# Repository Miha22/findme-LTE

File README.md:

# Low power LTE & GNSS anti-theft tracker

This project contains hardware design files, including schematics and PCB layouts created by Deniel.  
It is shared for educational and personal use purposes only. Commercial use is not permitted without written permission.

## Preview

The previews of the PCB design and schematic:

>  Note: The project is ongoing
> 1. Current schematic revision v0.3
> 2. Current PCB revision v0.1

## Description
Very compact __(20mm x 90mm)__ LTE modem designed to be used as anti-theft geolocation tracker to be mounted inside bicycles, moto, scooters etc. The UDP server and client to be setup and installed.

## Main Hardware
- MCU: STM32L433CCT6
- LTE: SIM7020**E**
- GNSS: ATGM336H-6N-74

## Notes for You
1. The design is still in Alpha state. New updates and revisions coming.
2. Firmware to be developed and tested as well as remote UDP server.
3. Real life Antenna test and adjustments needed, impedance matching has to be tuned (footprints are present).
4. Includes Design Rules errors due to **extreme size constraints**, take that in mind evaluating/redesigning the PCB. Keep width <25mm. 
5. All parts' datasheets have been analyzed. 
6. All parts are in stock on jlcpcb.com (except SIM7020E, but available on aliexpress for 9$+shipping).
7. Many drafts schematics are included in backups for you to see. Many failed because of incompatibility.

## License
This project is provided under a custom license based on the MIT License.  
Commercial use is prohibited. See the [LICENSE](./LICENSE) file for full details.

---

**Copyright © 2025 Deniel A.**

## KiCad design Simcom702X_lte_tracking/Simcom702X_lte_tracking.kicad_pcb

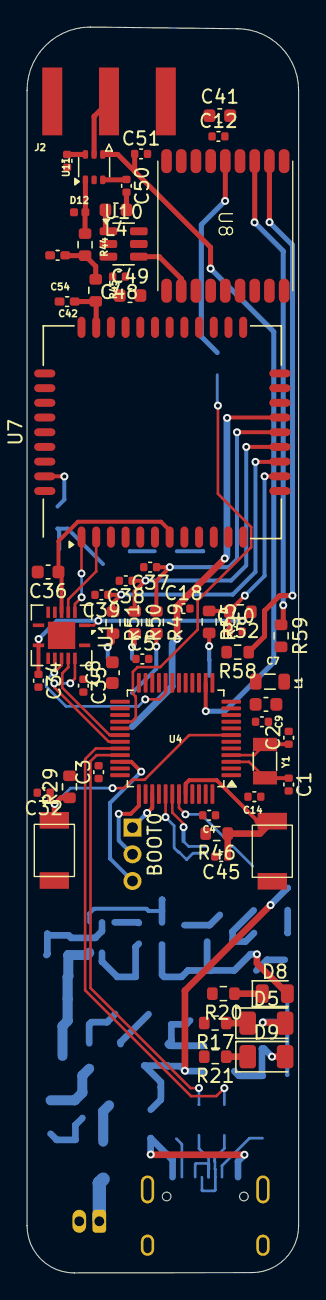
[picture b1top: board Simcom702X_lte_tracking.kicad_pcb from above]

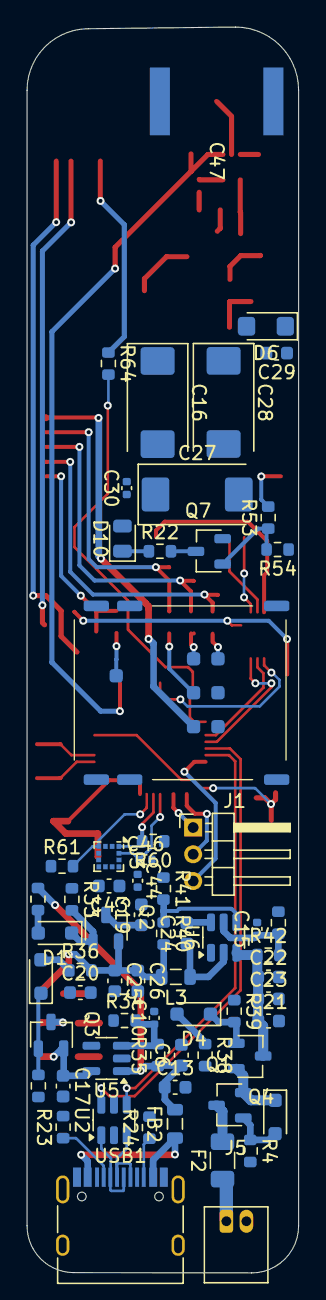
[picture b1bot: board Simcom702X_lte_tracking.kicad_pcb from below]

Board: 4 copper layers, 20.3 x 93.2 mm, 122 parts (64 on the bottom side), 78 nets.

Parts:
BOOT0: TS-1088-AR02016; SPST_39x30mm
C1, C2: 15p; C_0402_1005Metric
C3, C4, C5, C12, C14, C18, C30, C32, C34, C35, C40, C44, C45, C46, C47, C48: 0.1u; C_0402_1005Metric
C6, C7, C17, C29, C49: 1u; C_0603_1608Metric
C8: 4.7u; C_0603_1608Metric
C9: 0.01u; C_0402_1005Metric
C10, C15: 1n; C_0402_1005Metric
C13, C19, C20, C21, C24, C36: 0.1u; C_0603_1608Metric
C16, C27, C28: 100u; CP_EIA-7343-31_Kemet-D
C22, C23, C41, C43: 10u; C_0603_1608Metric
C25, C26: 22u; C_0603_1608Metric
C37, C38, C39: 22p; C_0402_1005Metric
C42, C54: 0u; C_0402_1005Metric_Pad0.74x0.62mm_HandSolder
C50: 470p; C_0402_1005Metric
C51: 100p; C_0402_1005Metric
D1: 1N5819WS; D_SOD-323_HandSoldering
D2: MM3Z10; D_SOD-323_HandSoldering
D3, D4: 1N5817WS; D_SOD-323_HandSoldering
D5: XL-3216SURC; LED_1206_3216Metric
D6: SMF6.0A; D_SMF
D8: XL-2012UYC; LED_0805_2012Metric
D9: XL-3216UOC; LED_1206_3216Metric
D10: XL-2012UBC-A; LED_0805_2012Metric
D12: LXES15AAA1-153; DFN1006-2L-BI
F2: JFC1206-1500FS; Fuse_1206_3216Metric
FB2: CBW201209U152T; L_0805_2012Metric
J1: SWD; PinHeader_1x03_P2.00mm_Horizontal
J2: SMA; SMA_Amphenol_132289_EdgeMount
J4: SNO-1470; nanoSIM_SNO-1470
J5: S2B-ZR-3.4(LF)(SN); JST_ZH_S2B-ZR_1x02_P1.50mm_Horizontal
L1: 39n; L_0805_2012Metric
L3: 4.7u; L_0805_2012Metric
L4: 7.5n; L_0603_1608Metric
NRST1: TS-1088-AR02016; SPST_39x30mm
Q1, Q2, Q3, Q4: AO3401A; SOT-23
Q7: AO3400A; SOT-23
R4, R33, R34, R37, R39, R43: 100k; R_0603_1608Metric
R17, R20, R21: 220; R_0603_1608Metric
R22, R58, R59: 100; R_0603_1608Metric
R23, R24: 5.1k; R_0603_1608Metric
R29, R32, R35, R36, R38, R41, R42, R46, R52, R60, R61: 10k; R_0603_1608Metric
R40: 33.2k; R_0603_1608Metric
R44, R45: 0; R_0603_1608Metric
R49, R50, R51: 22; R_0603_1608Metric
R53: 4.7k; R_0603_1608Metric
R54: 47k; R_0603_1608Metric
R55, R64: 1k; R_0603_1608Metric
U1: TXB0104RGYR; Texas_S-PVQFN-N14
U2: USBLC6-2SC6; SOT-23-6
U3: LIS2DW12TR; LGA-12_2x2mm_P0.5mm
U4: STM32L433CCT6; LQFP-48_7x7mm_P0.5mm
U5: TPRT9013-33GB; SOT-23-5
U6: TPS563201DDCR; SOT-23-6
U7: SIM7020E; SIMCom_SIM800C
U8: ATGM336H-6N-74; SMD_9.7x10.1mm_ATGM336H-6N-74
U10: AT2659S; SOT-23-6
U11: PE4259-63; SOT-363_SC-70-6
USB1: USB_C_Receptacle_USB2.0_16P; USB_C_Receptacle_HRO_TYPE-C-31-M-12
Y1: H31003271C2070CY; Crystal_SMD_3215-2Pin_3.2x1.5mm

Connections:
3V3a: C14.1, C25.1, C26.1, D8.2 (A), L3.2, Q2.2 (S), R36.2, R40.2, U4.1 (VBAT)
3V3b: C17.1, D9.2 (A), Q3.2 (S), U5.5 (VOUT)
+3.3V: BOOT0.1 (A), C3.1, C4.1, C5.1, C8.1, C12.1, C16.1, C19.1, C20.1, C27.1, C28.1, C29.1, C30.1, C35.1, C41.1, C43.1, C44.1, C48.1, C49.1, D5.2 (A), D6.1 (A1), D10.2 (A), L1.1, Q2.3 (D), Q3.3 (D), R29.2, R60.1, R61.1, U1.14 (VCCB), U3.2 (CS), U3.9 (VDD), U3.10 (VDDIO), U4.24 (VDD), U4.36 (VDDUSB), U4.48 (VDD), U7.9 (VDD_3V3), U7.34 (VBAT), U7.35 (VBAT), U8.6 (VBAT), U8.8 (VCC), U10.6 (VDD)
+3.3VA: C7.1, C9.1, L1.2, U4.9 (VDDA)
+5VBUS: C6.1, C13.1, FB2.2, R32.2, R35.1, R38.2, U2.5 (VBUS), U5.1 (VIN)
/ACC_EXTI: C46.1, U3.12 (INT1), U4.41 (PB5)
/ACC_SCL: R60.2, U3.1 (SCL/SPC), U4.42 (PB6)
/ACC_SDA: R61.2, U3.4 (SDA/SDI), U4.43 (PB7)
/BOOT0: BOOT0.2 (B), C45.1, R46.1, U4.44 (PH3)
/CC1: R23.1, USB1.A5 (CC1)
/CC2: R24.1, USB1.B5 (CC2)
/GNSS_RX: R59.1, U8.3 (RXD0)
/GNSS_SW: R64.2, U4.28 (PB15)
/GNSS_TX: R58.1, U8.2 (TXD0)
/LNA_SW: U4.29 (PA8), U10.5 (SHDN#)
/LTE_RI: C36.1, U1.4 (A3), U7.7 (UART1_RI)
/LTE_RX: U1.3 (A2), U7.2 (UART1_RXD)
/LTE_TX: U1.2 (A1), U7.1 (UART1_TXD)
/NETSTAT: R53.2, U7.41 (NETLIGHT)
/NRST: C32.1, NRST1.2 (B), R29.1, U4.7 (NRST)
/OSC_IN: C1.1, U4.3 (PC14), Y1.2
/OSC_OUT: C2.1, U4.4 (PC15), Y1.1
/RFIN: L4.2, U10.1 (RFIN)
/RF_GNSS: U8.11 (RF_IN), U10.4 (RFOUT)
/RF_J1: D12.2 (A2), R44.1, U11.1 (J3)
/RF_J2: C50.1, U11.3 (J2)
/RF_LTE: C42.1, R45.2, U7.32 (ANT)
/RF_SIG: C51.1, U4.14 (PA4), U11.4 (V1)
/RI_3V3: U1.11 (B3), U4.20 (PB2)
/SIM_CLK: C38.1, R50.1, U7.16 (SIM_CLK)
/SIM_DATA: C39.1, R51.1, U7.15 (SIM_DATA)
/SIM_DET: C40.1, R52.2, R55.1, U7.14 (SIM_DET)
/SIM_RST: C37.1, R49.1, U7.17 (SIM_RST)
/SWCLK: J1.2, U4.37 (PA14)
/SWDIO: J1.3, U4.34 (PA13)
/SWOUT: J1.1, U4.39 (PB3)
/UART1_RX: U1.13 (B1), U4.31 (PA10)
/UART1_TX: U1.12 (B2), U4.30 (PA9)
/UART2_RX: R58.2, U4.13 (PA3)
/UART2_TX: R59.2, U4.12 (PA2)
/USB_N: U2.1 (I/O1), U2.6 (I/O1), U4.32 (PA11), USB1.A7 (D-), USB1.B7 (D-)
/USB_P: U2.3 (I/O2), U2.4 (I/O2), U4.33 (PA12), USB1.A6 (D+), USB1.B6 (D+)
/WAKEUP: U4.19 (PB1), U7.12 (RTC_EINT)
GND: C1.2, C2.2, C3.2, C4.2, C5.2, C6.2, C7.2, C8.2, C9.2, C10.2, C12.2, C13.2, C14.2, C15.2, C16.2, C17.2, C18.2, C19.2, C20.2, C21.2, C22.2, C23.2, C25.2, C26.2, C27.2, C28.2, C29.2, C30.2, C32.2, C34.2, C35.2, C36.2, C37.2, C38.2, C39.2, C40.2, C41.2, C42.2, C43.2, C44.2, C45.2, C46.2, C47.2, C48.2, C49.2, C51.2, C54.2, D6.2 (A2), D12.1 (A1), J2.2 (Ext), J4.2 (GND), J4.3 (GND), J4.4 (GND), J4.5 (GND), J4.6 (GND), J4.7 (GND), J4.C5 (GND), J5.2, NRST1.1 (A), Q7.2 (S), R4.2, R17.2, R20.2, R21.2, R23.2, R24.2, R33.1, R34.1, R37.1, R39.1, R41.1, R43.1, R46.2, R54.1, U1.7 (GND), U1.15 (Pad), U2.2 (GND), U3.3 (SA0/SDO), U3.6 (GND), U3.7 (RES), U3.8 (GND), U4.8 (VSSA), U4.23 (VSS), U4.35 (VSS), U4.47 (VSS), U5.2 (GND), U6.1 (GND), U7.8 (GND), U7.13 (GND), U7.19 (GND), U7.21 (GND), U7.27 (GND), U7.30 (GND), U7.31 (GND), U7.33 (GND), U7.36 (GND), U7.37 (GND), U8.1 (GND), U8.10 (GND), U8.12 (GND), U10.2 (GND), U10.3 (GND), U11.2 (GND), USB1.A1 (GND), USB1.A12 (GND), USB1.B1 (GND), USB1.B12 (GND)
unnamed: C50.2, L4.1
unnamed: C54.1, R44.2, R45.1
unnamed: D1.2 (A), R32.1
unnamed: D1.1 (K), Q2.1 (G), R33.2
unnamed: D2.2 (A), Q1.1 (G), R4.1
unnamed: D3.2 (A), R36.1
unnamed: D3.1 (K), Q3.1 (G), R37.2
unnamed: D4.2 (A), R38.1
unnamed: D4.1 (K), Q4.1 (G), R39.2
unnamed: D5.1 (K), R17.1
unnamed: D8.1 (K), R20.1
unnamed: D9.1 (K), R21.1
unnamed: D10.1 (K), R22.1
unnamed: J2.1 (In), U11.5 (J1)
unnamed: J4.C3 (CLK), R50.2
unnamed: J4.C7 (I/O), R51.2
unnamed: J4.C2 (RST), R49.2
unnamed: J4.1 (SW), R55.2
unnamed: F2.2, Q1.3 (D)
unnamed: Q7.3 (D), R22.2
unnamed: Q7.1 (G), R53.1, R54.2
unnamed: C10.1, R34.2, R35.2, U5.3 (EN)
unnamed: C15.1, R42.2, R43.2, U6.5 (EN)
unnamed: C24.1, L3.1, U6.2 (SW)
unnamed: C24.2, U6.6 (VBST)
unnamed: R40.1, R41.2, U6.4 (VFB)
unnamed: R64.1, U8.5 (ON/OFF)
RF_PWR: C47.1, U11.6 (V2)
SIM_VCC: C18.1, J4.C1 (VCC), U7.18 (SIM_VDD)
VBUS: FB2.1, USB1.A4 (VBUS), USB1.A9 (VBUS), USB1.B4 (VBUS), USB1.B9 (VBUS)
VDDEXT: C34.1, R52.1, U1.1 (VCCA), U1.8 (OE), U7.40 (VDD_EXT)
VIN: C21.1, C22.1, C23.1, Q4.3 (D), R42.1, U6.3 (VIN)
VINa: D2.1 (K), Q1.2 (S), Q4.2 (S)
VLIPO: F2.1, J5.1

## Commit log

2025-04-18 Sch.Rev.03 PCB.Rev.01
